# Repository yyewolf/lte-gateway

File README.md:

# lte-gateway

A self-hosted LTE SMS + voice gateway: an ESP32-S3 board with a SIMCom LTE Cat-1 modem
(VoLTE) that joins a Tailscale tailnet over WiFi. It sends and receives SMS and relays
calls as an RTP audio stream. All the heavy logic (Discord bridge, recording, SIP) runs on
a separate machine on the tailnet.

## Layout

| Folder | What |
|---|---|
| `firmware/` | ESP-IDF firmware for the gateway board |
| `hardware/` | KiCad project for the board and its fabrication files ([README](hardware/README.md)) |
| `server/` | Go server: Discord bridge for SMS, calls and call audio ([README](server/README.md)) |
| `case/` | 3D-printable snap-fit enclosure ([README](case/README.md)) |

## Pictures

| Assembly without the lid | Assembly with the lid on |
|---|---|
|  |  |

## Sponsorship

JLCPCB sponsored the PCB fabrication and assembly for this project: I paid much less than the
normal price for the rev 0.6 boards. They have no say in what I write here, and I'm free to
say anything about them, good or bad.

## License

The firmware, server, hardware and case here are BSD 3-Clause, see [LICENSE](LICENSE).

Tailscale compatibility does not come from Tailscale: `firmware/components/microlink` is
vendored from [CamM2325/microlink](https://github.com/CamM2325/microlink) (MIT, upstream
commit 216da33), a reverse-engineered implementation of the Tailscale protocol for embedded
devices, unaffiliated with and not endorsed by Tailscale Inc. The vendored copy carries
local patches (listed in
[firmware/components/VENDORED.txt](firmware/components/VENDORED.txt)), so it is committed
here rather than fetched at build time. `firmware/components/wireguard_lwip` and the x25519
sources keep their own licenses, included next to the code.

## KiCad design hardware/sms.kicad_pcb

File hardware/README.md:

# Hardware

ESP32-S3-WROOM-1 + SIMCom A7670E-LASE gateway board, KiCad 10.

- 4 layers, 99.9 x 99.9 mm, JLC04161H-7628 stackup, ENIG
- Open `sms.kicad_pro`. The JLC symbols, footprints and 3D models are in `lib/`.
- `sms-schematic.pdf` is the schematic exported as a PDF (re-export with `kicad-cli sch export pdf -o sms-schematic.pdf sms.kicad_sch` after edits).
- `schematic-notes.md` has the design notes that used to sit as text on the schematic sheets.
- `fab/rev0.6/` holds the Gerbers, BOM and CPL used for the JLCPCB order.

PCB fabrication and assembly sponsored by JLCPCB.

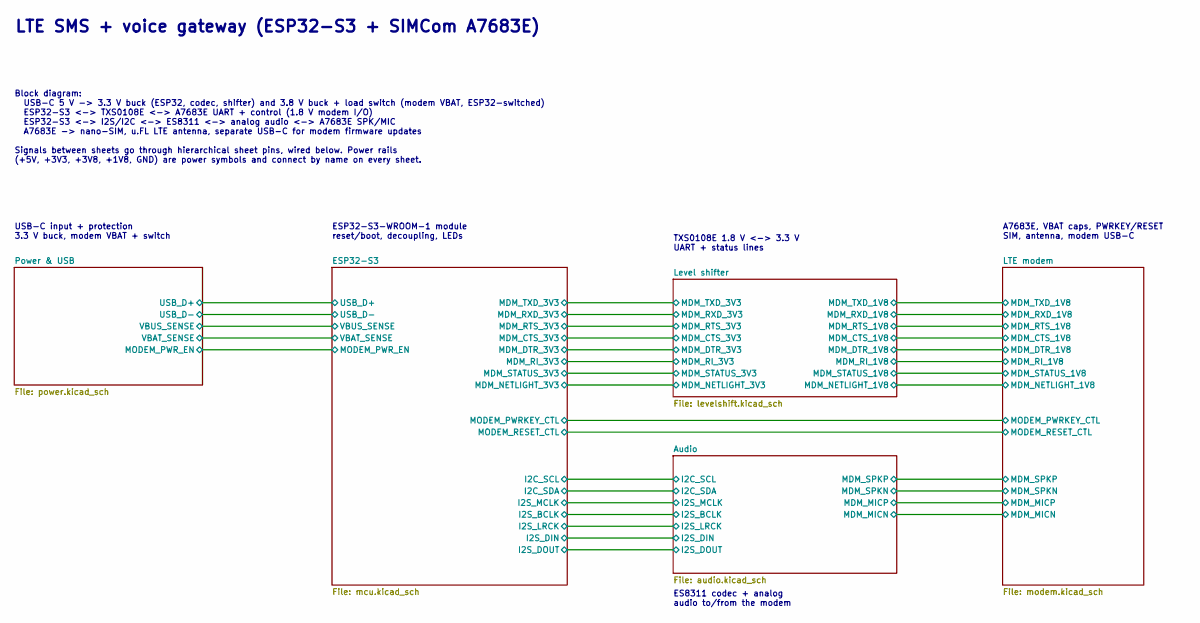
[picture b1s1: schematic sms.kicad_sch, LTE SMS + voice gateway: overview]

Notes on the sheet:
USB-C input + protection 3.3 V buck, modem VBAT + switch
LTE SMS + voice gateway (ESP32-S3 + SIMCom A7683E)
ESP32-S3-WROOM-1 module reset/boot, decoupling, LEDs
A7683E, VBAT caps, PWRKEY/RESET SIM, antenna, modem USB-C
Block diagram: USB-C 5 V -> 3.3 V buck (ESP32, codec, shifter) and 3.8 V buck + load switch (modem VBAT, ESP32-switched) ESP32-S3 <-> TXS0108E <-> A7683E UART + control (1.8 V modem I/O) ESP32-S3 <-> I2S/I2C <-> ES8311 <-> analog audio <-> A7683E SPK/MIC A7683E -> nano-SIM, u.FL LTE antenna, separa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
TXS0108E 1.8 V <-> 3.3 V UART + status lines
ES8311 codec + analog audio to/from the modem

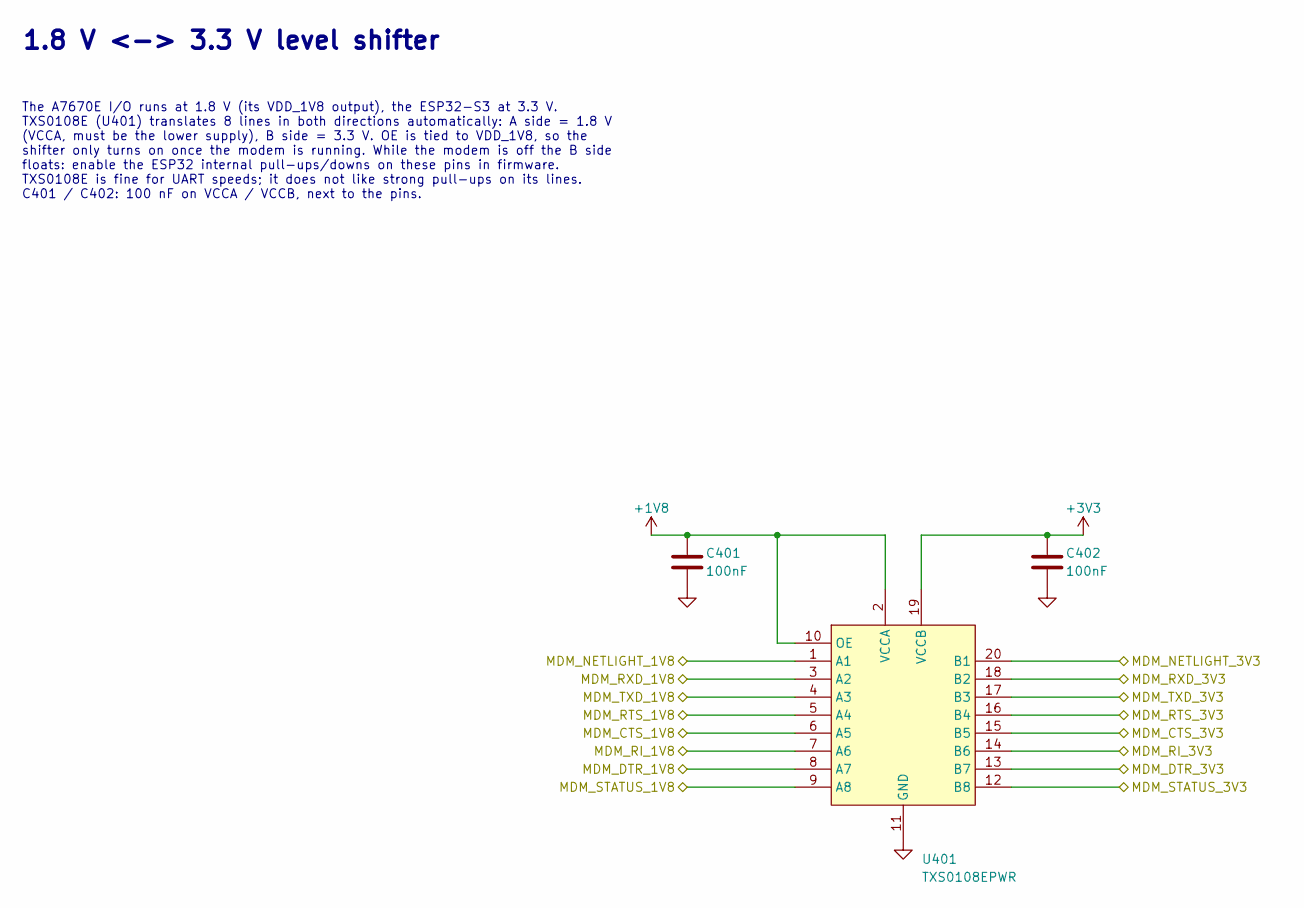
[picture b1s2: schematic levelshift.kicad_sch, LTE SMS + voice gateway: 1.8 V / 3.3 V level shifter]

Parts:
C401, C402: 100nF; C_0402_1005Metric; MPN CL05B104KO5NNNC; LCSC Part C1525
U401: TXS0108EPWR; TSSOP-20_L6.5-W4.4-P0.65-LS6.4-BL; MPN TXS0108EPWR; LCSC Part C17206

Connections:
+1V8: C401.1, U401.2 (VCCA), U401.10 (OE); also elsewhere on the board
+3V3: C402.1, U401.19 (VCCB); also elsewhere on the board
/ESP32-S3/MDM_CTS_3V3: U401.15 (B5); also elsewhere on the board
/ESP32-S3/MDM_DTR_3V3: U401.13 (B7); also elsewhere on the board
/ESP32-S3/MDM_NETLIGHT_3V3: U401.20 (B1); also elsewhere on the board
/ESP32-S3/MDM_RI_3V3: U401.14 (B6); also elsewhere on the board
/ESP32-S3/MDM_RTS_3V3: U401.16 (B4); also elsewhere on the board
/ESP32-S3/MDM_RXD_3V3: U401.18 (B2); also elsewhere on the board
/ESP32-S3/MDM_STATUS_3V3: U401.12 (B8); also elsewhere on the board
/ESP32-S3/MDM_TXD_3V3: U401.17 (B3); also elsewhere on the board
/LTE modem/MDM_CTS_1V8: U401.6 (A5); also elsewhere on the board
/LTE modem/MDM_DTR_1V8: U401.8 (A7); also elsewhere on the board
/LTE modem/MDM_NETLIGHT_1V8: U401.1 (A1); also elsewhere on the board
/LTE modem/MDM_RI_1V8: U401.7 (A6); also elsewhere on the board
/LTE modem/MDM_RTS_1V8: U401.5 (A4); also elsewhere on the board
/LTE modem/MDM_RXD_1V8: U401.3 (A2); also elsewhere on the board
/LTE modem/MDM_STATUS_1V8: U401.9 (A8); also elsewhere on the board
/LTE modem/MDM_TXD_1V8: U401.4 (A3); also elsewhere on the board
GND: C401.2, C402.2, U401.11 (GND); also elsewhere on the board

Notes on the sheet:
The A7670E I/O runs at 1.8 V (its VDD_1V8 output), the ESP32-S3 at 3.3 V. TXS0108E (U401) translates 8 lines in both directions automatically: A side = 1.8 V (VCCA, must be the lower supply), B side = 3.3 V. OE is tied to VDD_1V8, so the shifter only turns on once the modem is running. While the mo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
1.8 V <-> 3.3 V level shifter

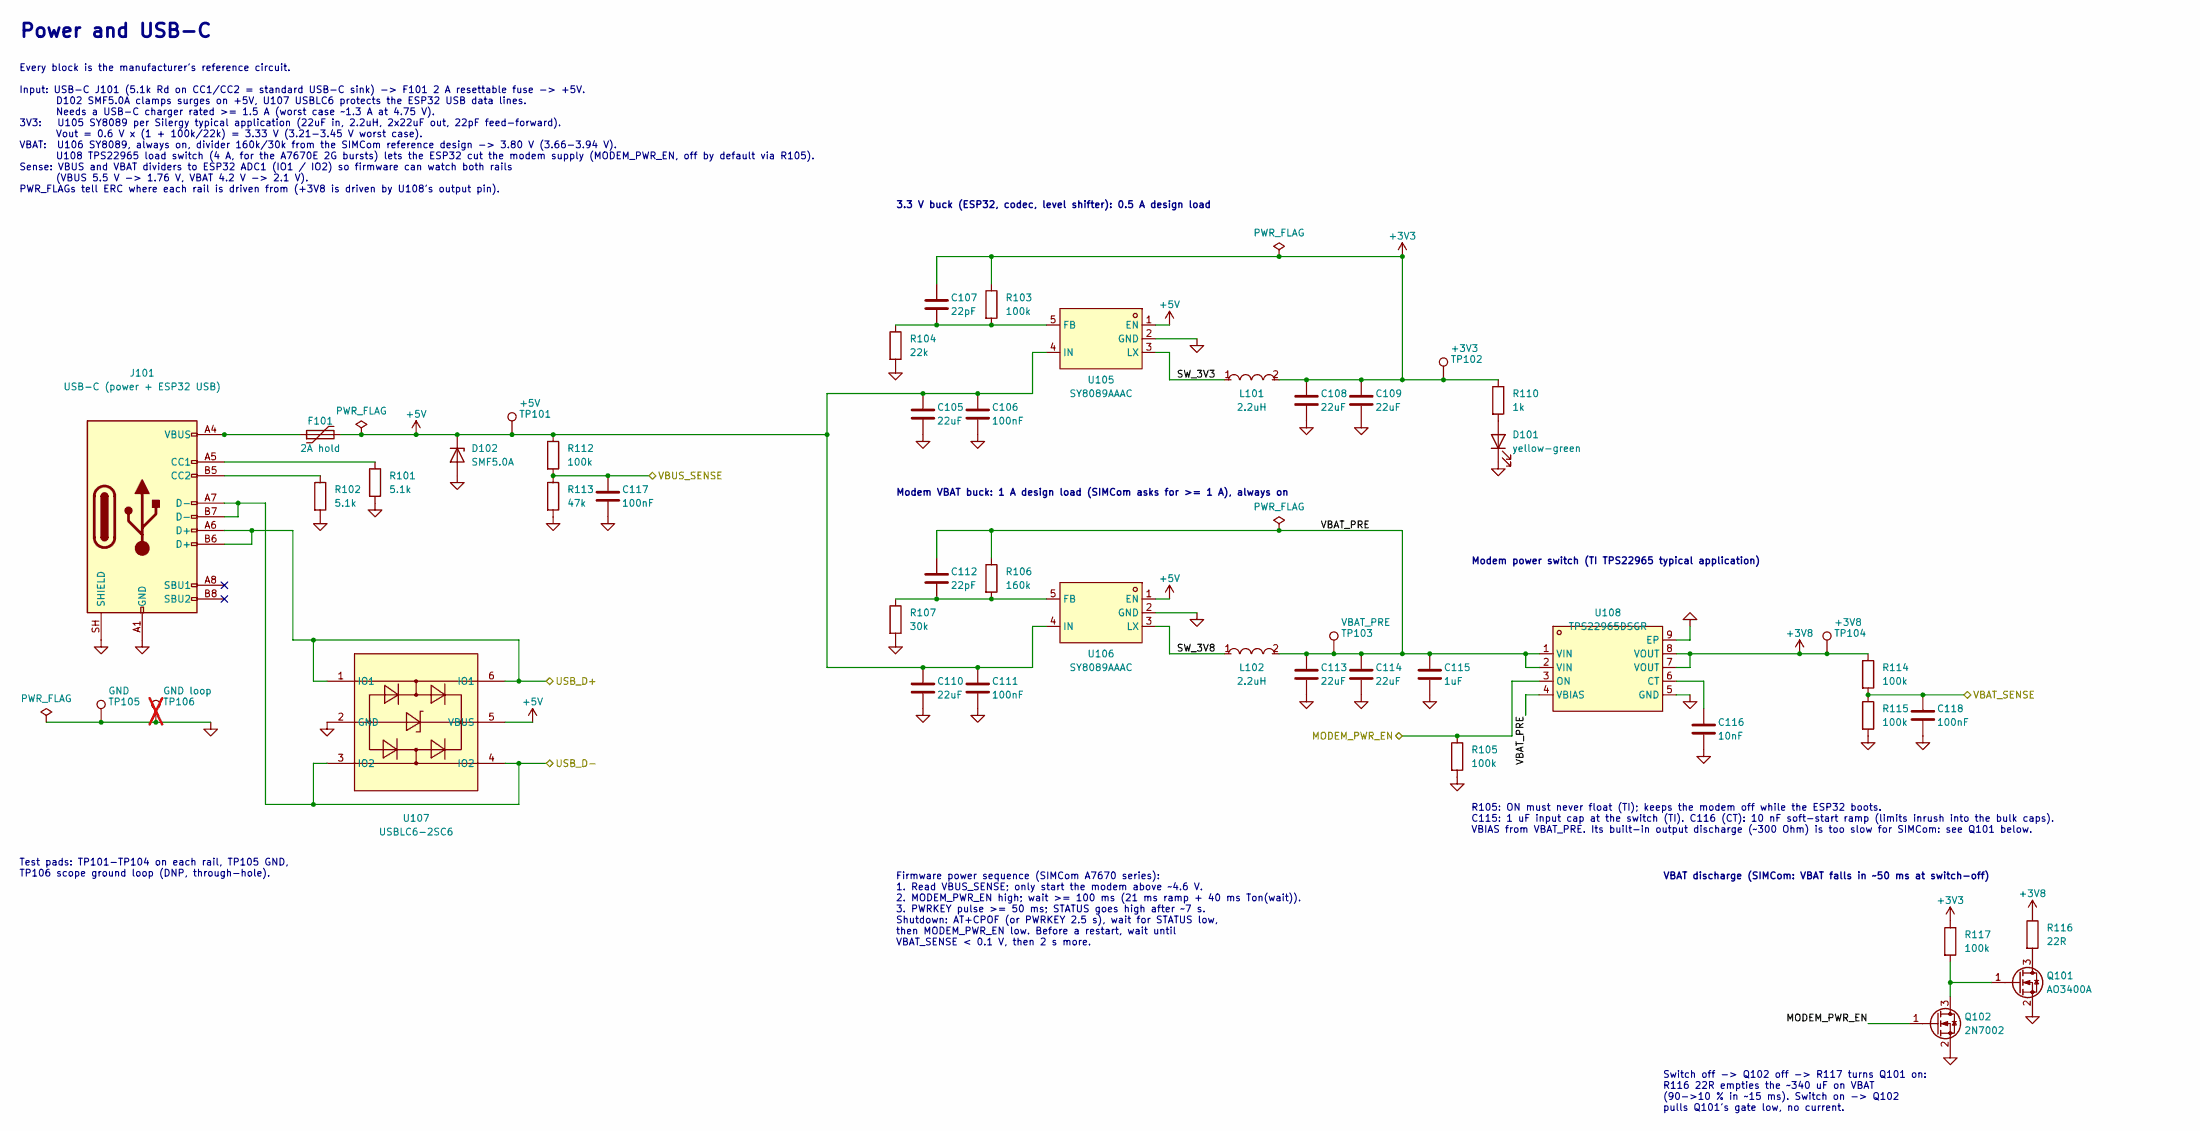
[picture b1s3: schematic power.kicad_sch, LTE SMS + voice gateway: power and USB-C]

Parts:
C105, C108, C109, C110, C113, C114: 22uF; C_0805_2012Metric; MPN CL21A226MAQNNNE; LCSC Part C45783
C106, C111, C117, C118: 100nF; C_0402_1005Metric; MPN CL05B104KO5NNNC; LCSC Part C1525
C107, C112: 22pF; C_0402_1005Metric; MPN 0402CG220J500NT; LCSC Part C1555
C115: 1uF; C_0402_1005Metric; MPN CL05A105KA5NQNC; LCSC Part C52923
C116: 10nF; C_0402_1005Metric; MPN CL05B103KB5NNNC; LCSC Part C15195
D101: yellow-green; LED_0603_1608Metric; MPN KT-0603YG; LCSC Part C2289
D102: SMF5.0A; D_SOD-123F; MPN SMF5.0A; LCSC Part C193402
F101: 2A hold; Fuse_1206_3216Metric; MPN SMD1206P200TF; LCSC Part C20988
J101: USB-C (power + ESP32 USB); USB_C_Receptacle_HRO_TYPE-C-31-M-12; MPN TYPE-C-31-M-12; LCSC Part C165948
L101, L102: 2.2uH; IND-SMD_L4.0-W4.0_FNR40XXS; MPN FNR4030S2R2MT; LCSC Part C167869
Q101: AO3400A; SOT-23-3_L2.9-W1.3-P1.90-LS2.4-BR; MPN AO3400A; LCSC Part C20917
Q102: 2N7002; SOT-23-3_L2.9-W1.3-P1.90-LS2.4-BR; MPN 2N7002; LCSC Part C8545
R101, R102: 5.1k; R_0402_1005Metric; MPN 0402WGF5101TCE; LCSC Part C25905
R103, R105, R112, R114, R115, R117: 100k; R_0402_1005Metric; MPN 0402WGF1003TCE; LCSC Part C25741
R104: 22k; R_0402_1005Metric; MPN 0402WGF2202TCE; LCSC Part C25768
R106: 160k; R_0402_1005Metric; MPN 0402WGF1603TCE; LCSC Part C25757
R107: 30k; R_0402_1005Metric; MPN 0402WGF3002TCE; LCSC Part C25776
R110: 1k; R_0402_1005Metric; MPN 0402WGF1001TCE; LCSC Part C11702
R113: 47k; R_0402_1005Metric; MPN 0402WGF4702TCE; LCSC Part C25792
R116: 22R; R_0805_2012Metric; MPN 0805W8F220JT5E; LCSC Part C17561
TP101: +5V; TestPoint_Pad_D1.5mm; MPN test pad
TP102: +3V3; TestPoint_Pad_D1.5mm; MPN test pad
TP103: VBAT_PRE; TestPoint_Pad_D1.5mm; MPN test pad
TP104: +3V8; TestPoint_Pad_D1.5mm; MPN test pad
TP105: GND; TestPoint_Pad_D1.5mm; MPN test pad
TP106: GND loop; TestPoint_Keystone_5000-5004_Miniature; MPN Keystone 5001; not fitted
U105, U106: SY8089AAAC; SOT-23-5_L3.0-W1.7-P0.95-LS2.8-BR; MPN SY8089AAAC; LCSC Part C78988
U107: USBLC6-2SC6; SOT-23-6_L2.9-W1.6-P0.95-LS2.8-BL; MPN USBLC6-2SC6; LCSC Part C7519
U108: TPS22965DSGR; UDFN-8_L2.0-W2.0-P0.50-TL-EP; MPN TPS22965DSGR; LCSC Part C122837

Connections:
+3V3: C107.1, C108.1, C109.1, L101.2, R103.1, R110.1, R117.1, TP102.1; also elsewhere on the board
+3V8: R114.1, R116.1, TP104.1, U108.7 (VOUT), U108.8 (VOUT); also elsewhere on the board
+5V: C105.1, C106.1, C110.1, C111.1, D102.1 (K), F101.2, R112.1, TP101.1, U105.1 (EN), U105.4 (IN), U106.1 (EN), U106.4 (IN), U107.5 (VBUS)
/ESP32-S3/USB_D+: J101.A6 (D+), J101.B6 (D+), U107.1 (IO1), U107.6 (IO1); also elsewhere on the board
/ESP32-S3/USB_D-: J101.A7 (D-), J101.B7 (D-), U107.3 (IO2), U107.4 (IO2); also elsewhere on the board
/ESP32-S3/VBAT_SENSE: C118.1, R114.2, R115.1; also elsewhere on the board
/ESP32-S3/VBUS_SENSE: C117.1, R112.2, R113.1; also elsewhere on the board
/Power & USB/MODEM_PWR_EN: Q102.1 (G), R105.1, U108.3 (ON); also elsewhere on the board
/Power & USB/SW_3V3: L101.1, U105.3 (LX)
/Power & USB/SW_3V8: L102.1, U106.3 (LX)
/Power & USB/VBAT_PRE: C112.1, C113.1, C114.1, C115.1, L102.2, R106.1, TP103.1, U108.1 (VIN), U108.2 (VIN), U108.4 (VBIAS)
GND: C105.2, C106.2, C108.2, C109.2, C110.2, C111.2, C113.2, C114.2, C115.2, C116.2, C117.2, C118.2, D101.1 (K), D102.2 (A), J101.A1 (GND), J101.A12 (GND), J101.B1 (GND), J101.B12 (GND), J101.SH (SHIELD), Q101.2 (S), Q102.2 (S), R101.2, R102.2, R104.2, R105.2, R107.2, R113.2, R115.2, TP105.1, TP106.1, U105.2 (GND), U106.2 (GND), U107.2 (GND), U108.5 (GND), U108.9 (EP); also elsewhere on the board
unnamed: D101.2 (A), R110.2
unnamed: F101.1, J101.A4 (VBUS), J101.A9 (VBUS), J101.B4 (VBUS), J101.B9 (VBUS)
unnamed: J101.A5 (CC1), R101.1
unnamed: J101.B5 (CC2), R102.1
unnamed: Q101.3 (D), R116.2
unnamed: Q101.1 (G), Q102.3 (D), R117.2
unnamed: C107.2, R103.2, R104.1, U105.5 (FB)
unnamed: C112.2, R106.2, R107.1, U106.5 (FB)
unnamed: C116.1, U108.6 (CT)

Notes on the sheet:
Power and USB-C
Every block is the manufacturer's reference circuit. Input: USB-C J101 (5.1k Rd on CC1/CC2 = standard USB-C sink) -> F101 2 A resettable fuse -> +5V. D102 SMF5.0A clamps surges on +5V, U107 USBLC6 protects the ESP32 USB data lines. Needs a USB-C charger rated >= 1.5 A (worst case ~1.3 A at 4.75 V).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
3.3 V buck (ESP32, codec, level shifter): 0.5 A design load
Modem VBAT buck: 1 A design load (SIMCom asks for >= 1 A), always on
Modem power switch (TI TPS22965 typical application)
R105: ON must never float (TI); keeps the modem off while the ESP32 boots. C115: 1 uF input cap at the switch (TI). C116 (CT): 10 nF soft-start ramp (limits inrush into the bulk caps). VBIAS from VBAT_PRE. Its built-in output discharge (~300 Ohm) is too slow for SIMCom: see Q101 below.
VBAT discharge (SIMCom: VBAT falls in ~50 ms at switch-off)
Switch off -> Q102 off -> R117 turns Q101 on: R116 22R empties the ~340 uF on VBAT (90->10 % in ~15 ms). Switch on -> Q102 pulls Q101's gate low, no current.
Firmware power sequence (SIMCom A7670 series): 1. Read VBUS_SENSE; only start the modem above ~4.6 V. 2. MODEM_PWR_EN high; wait >= 100 ms (21 ms ramp + 40 ms Ton(wait)). 3. PWRKEY pulse >= 50 ms; STATUS goes high after ~7 s. Shutdown: AT+CPOF (or PWRKEY 2.5 s), wait for STATUS low, then MODEM_PWR_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
Test pads: TP101-TP104 on each rail, TP105 GND, TP106 scope ground loop (DNP, through-hole).

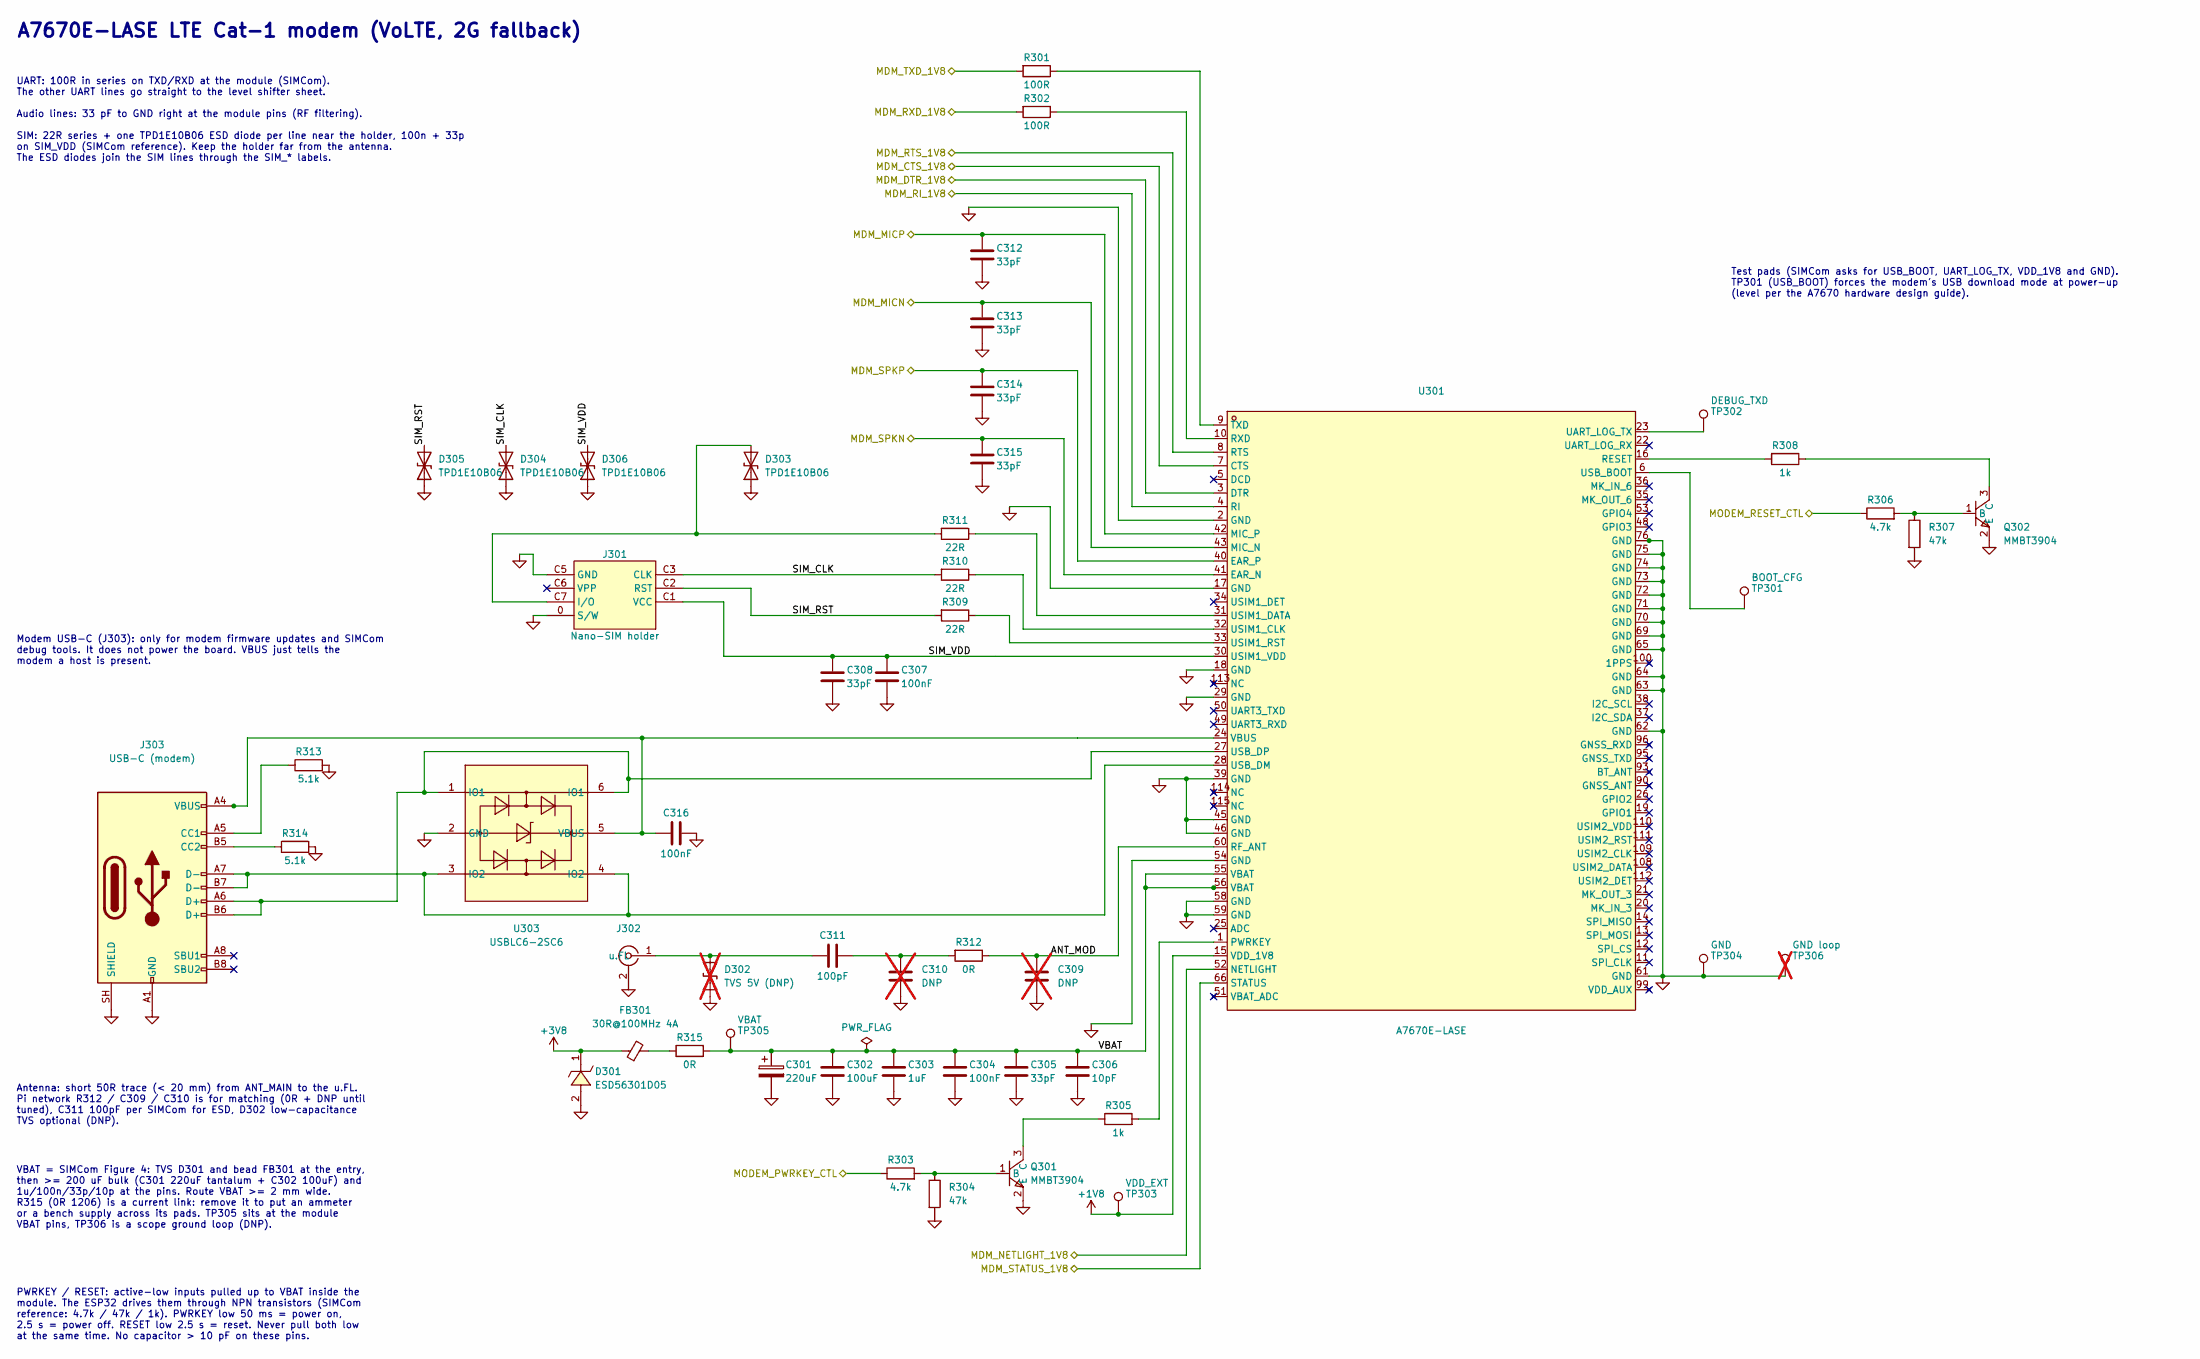
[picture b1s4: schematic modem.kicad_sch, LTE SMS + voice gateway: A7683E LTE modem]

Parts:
C301: 220uF; CP_EIA-7343-31_Kemet-D; MPN TAJD227K010RNJ (220uF 10V tantalum, 500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; LCSC Part C8024
C302: 100uF; C_1206_3216Metric; MPN CL31A107MQHNNNE; LCSC Part C15008
C303: 1uF; C_0402_1005Metric; MPN CL05A105KA5NQNC; LCSC Part C52923
C304, C307, C316: 100nF; C_0402_1005Metric; MPN CL05B104KO5NNNC; LCSC Part C1525
C305, C308, C312, C313, C314, C315: 33pF; C_0402_1005Metric; MPN 0402CG330J500NT; LCSC Part C1562
C306: 10pF; C_0402_1005Metric; MPN CL05C100JB5NNNC; LCSC Part C32949
C309, C310: DNP; C_0402_1005Metric; MPN matching, value from antenna tuning; not fitted
C311: 100pF; C_0402_1005Metric; MPN 0402CG101J500NT; LCSC Part C1546
D301: ESD56301D05; DFN1610-2L_L1.6-W1.0-P1.10-RD; MPN ESD56301D05-2/TR; LCSC Part C2939837
D302: TVS 5V (DNP); D_SOD-323; MPN choose at review; not fitted
D303, D304, D305, D306: TPD1E10B06; X1SON-2_L1.0-W0.6-P0.65-BI-1; MPN TPD1E10B06DPYR; LCSC Part C48260
FB301: 30R@100MHz 4A; L_0805_2012Metric; MPN BLM21PG300SN1D; LCSC Part C16903
J301: Nano-SIM holder; SIM-SMD_C77877; MPN NANO SIM 6PIN; LCSC Part C2963104
J302: u.FL; U.FL_Hirose_U.FL-R-SMT-1_Vertical; MPN U.FL-R-SMT-1(80); LCSC Part C88374
J303: USB-C (modem); USB_C_Receptacle_HRO_TYPE-C-31-M-12; MPN TYPE-C-31-M-12; LCSC Part C165948
Q301, Q302: MMBT3904; SOT-23-3_L2.9-W1.3-P1.90-LS2.4-BR; MPN MMBT3904; LCSC Part C20526
R301, R302: 100R; R_0402_1005Metric; MPN 0402WGF1000TCE; LCSC Part C25076
R303, R306: 4.7k; R_0402_1005Metric; MPN 0402WGF4701TCE; LCSC Part C25900
R304, R307: 47k; R_0402_1005Metric; MPN 0402WGF4702TCE; LCSC Part C25792
R305, R308: 1k; R_0402_1005Metric; MPN 0402WGF1001TCE; LCSC Part C11702
R309, R310, R311: 22R; R_0402_1005Metric; MPN 0402WGF220JTCE; LCSC Part C25092
R312: 0R; R_0402_1005Metric; MPN 0402WGF0000TCE; LCSC Part C17168
R313, R314: 5.1k; R_0402_1005Metric; MPN 0402WGF5101TCE; LCSC Part C25905
R315: 0R; R_1206_3216Metric; MPN 1206W4F0000T5E; LCSC Part C17888
TP301: BOOT_CFG; TestPoint_Pad_D1.5mm; MPN test pad
TP302: DEBUG_TXD; TestPoint_Pad_D1.5mm; MPN test pad
TP303: VDD_EXT; TestPoint_Pad_D1.5mm; MPN test pad
TP304: GND; TestPoint_Pad_D1.5mm; MPN test pad
TP305: VBAT; TestPoint_Pad_D1.5mm
TP306: GND loop; TestPoint_Keystone_5000-5004_Miniature; MPN Keystone 5001; not fitted
U301: A7670E-LASE; LGA-124_L24.0-W24.0-P1.0-A7670C-LASS; MPN A7670E-LASE; LCSC Part C5362211
U303: USBLC6-2SC6; SOT-23-6_L2.9-W1.6-P0.95-LS2.8-BL; MPN USBLC6-2SC6; LCSC Part C7519

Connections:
+1V8: TP303.1, U301.15 (VDD_1V8); also elsewhere on the board
+3V8: D301.1 (K), FB301.1; also elsewhere on the board
/Audio/MDM_MICN: C313.1, U301.43 (MIC_N); also elsewhere on the board
/Audio/MDM_MICP: C312.1, U301.42 (MIC_P); also elsewhere on the board
/Audio/MDM_SPKN: C315.1, U301.41 (EAR_N); also elsewhere on the board
/Audio/MDM_SPKP: C314.1, U301.40 (EAR_P); also elsewhere on the board
/ESP32-S3/MODEM_PWRKEY_CTL: R303.1; also elsewhere on the board
/ESP32-S3/MODEM_RESET_CTL: R306.1; also elsewhere on the board
/LTE modem/ANT_MOD: C309.1, R312.1, U301.60 (RF_ANT)
/LTE modem/MDM_CTS_1V8: U301.7 (CTS); also elsewhere on the board
/LTE modem/MDM_DTR_1V8: U301.3 (DTR); also elsewhere on the board
/LTE modem/MDM_NETLIGHT_1V8: U301.52 (NETLIGHT); also elsewhere on the board
/LTE modem/MDM_RI_1V8: U301.4 (RI); also elsewhere on the board
/LTE modem/MDM_RTS_1V8: U301.8 (RTS); also elsewhere on the board
/LTE modem/MDM_RXD_1V8: R302.2; also elsewhere on the board
/LTE modem/MDM_STATUS_1V8: U301.66 (STATUS); also elsewhere on the board
/LTE modem/MDM_TXD_1V8: R301.2; also elsewhere on the board
/LTE modem/SIM_CLK: D304.2 (A2), J301.C3 (CLK), R310.2
/LTE modem/SIM_RST: D305.2 (A2), J301.C2 (RST), R309.2
/LTE modem/SIM_VDD: C307.1, C308.1, D306.2 (A2), J301.C1 (VCC), U301.30 (USIM1_VDD)
/LTE modem/VBAT: C301.1, C302.1, C303.1, C304.1, C305.1, C306.1, R315.2, TP305.1, U301.55 (VBAT), U301.56 (VBAT), U301.57 (VBAT)
GND: C301.2, C302.2, C303.2, C304.2, C305.2, C306.2, C307.2, C308.2, C309.2, C310.2, C312.2, C313.2, C314.2, C315.2, C316.2, D301.2 (A), D302.1 (A1), D303.1 (A1), D304.1 (A1), D305.1 (A1), D306.1 (A1), J301.0 (S/W), J301.C5 (GND), J302.2 (Ext), J303.A1 (GND), J303.A12 (GND), J303.B1 (GND), J303.B12 (GND), J303.SH (SHIELD), Q301.2 (E), Q302.2 (E), R304.2, R307.2, R313.2, R314.2, TP304.1, TP306.1, U301.2 (GND), U301.17 (GND), U301.18 (GND), U301.29 (GND), U301.39 (GND), U301.45 (GND), U301.46 (GND), U301.54 (GND), U301.58 (GND), U301.59 (GND), U301.61 (GND), U301.62 (GND), U301.63 (GND), U301.64 (GND), U301.65 (GND), U301.69 (GND), U301.70 (GND), U301.71 (GND), U301.72 (GND), U301.73 (GND), U301.74 (GND), U301.75 (GND), U301.76 (GND), U301.77 (GND), U301.78 (GND), U301.79 (GND), U301.80 (GND), U301.81 (GND), U301.82 (GND), U301.83 (GND), U301.84 (GND), U301.85 (GND), U301.86 (GND), U301.87 (GND), U301.88 (GND), U301.89 (GND), U301.91 (GND), U301.92 (GND), U301.94 (GND), U303.2 (GND); also elsewhere on the board
unnamed: C310.1, C311.1, R312.2
unnamed: C311.2, D302.2 (A2), J302.1 (In)
unnamed: D303.2 (A2), J301.C7 (I/O), R311.2
unnamed: FB301.2, R315.1
unnamed: J303.A5 (CC1), R313.1
unnamed: J303.B5 (CC2), R314.1
unnamed: Q301.1 (B), R303.2, R304.1
unnamed: Q301.3 (C), R305.1
unnamed: Q302.1 (B), R306.2, R307.1
unnamed: Q302.3 (C), R308.1
unnamed: R305.2, U301.1 (PWRKEY)
unnamed: R308.2, U301.16 (RESET)
unnamed: R302.1, U301.10 (RXD)
unnamed: R301.1, U301.9 (TXD)
unnamed: TP302.1, U301.23 (UART_LOG_TX)
unnamed: TP301.1, U301.6 (USB_BOOT)
unnamed: J303.A7 (D-), J303.B7 (D-), U301.28 (USB_DM), U303.3 (IO2), U303.4 (IO2)
unnamed: J303.A6 (D+), J303.B6 (D+), U301.27 (USB_DP), U303.1 (IO1), U303.6 (IO1)
unnamed: R310.1, U301.32 (USIM1_CLK)
unnamed: R311.1, U301.31 (USIM1_DATA)
unnamed: R309.1, U301.33 (USIM1_RST)
unnamed: C316.1, J303.A4 (VBUS), J303.A9 (VBUS), J303.B4 (VBUS), J303.B9 (VBUS), U301.24 (VBUS), U303.5 (VBUS)

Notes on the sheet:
A7670E-LASE LTE Cat-1 modem (VoLTE, 2G fallback)
UART: 100R in series on TXD/RXD at the module (SIMCom). The other UART lines go straight to the level shifter sheet. Audio lines: 33 pF to GND right at the module pins (RF filtering). SIM: 22R series + one TPD1E10B06 ESD diode per line near the holder, 100n + 33p on SIM_VDD (SIMCom reference). Keep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
Modem USB-C (J303): only for modem firmware updates and SIMCom debug tools. It does not power the board. VBUS just tells the modem a host is present.
Antenna: short 50R trace (< 20 mm) from ANT_MAIN to the u.FL. Pi network R312 / C309 / C310 is for matching (0R + DNP until tuned), C311 100pF per SIMCom for ESD, D302 low-capacitance TVS optional (DNP).
VBAT = SIMCom Figure 4: TVS D301 and bead FB301 at the entry, then >= 200 uF bulk (C301 220uF tantalum + C302 100uF) and 1u/100n/33p/10p at the pins. Route VBAT >= 2 mm wide. R315 (0R 1206) is a current link: remove it to put an ammeter or a bench supply across its pads. TP305 sits at the module VB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
PWRKEY / RESET: active-low inputs pulled up to VBAT inside the module. The ESP32 drives them through NPN transistors (SIMCom reference: 4.7k / 47k / 1k). PWRKEY low 50 ms = power on, 2.5 s = power off. RESET low 2.5 s = reset. Never pull both low at the same time. No capacitor > 10 pF on these pins.
Test pads (SIMCom asks for USB_BOOT, UART_LOG_TX, VDD_1V8 and GND). TP301 (USB_BOOT) forces the modem's USB download mode at power-up (level per the A7670 hardware design guide).

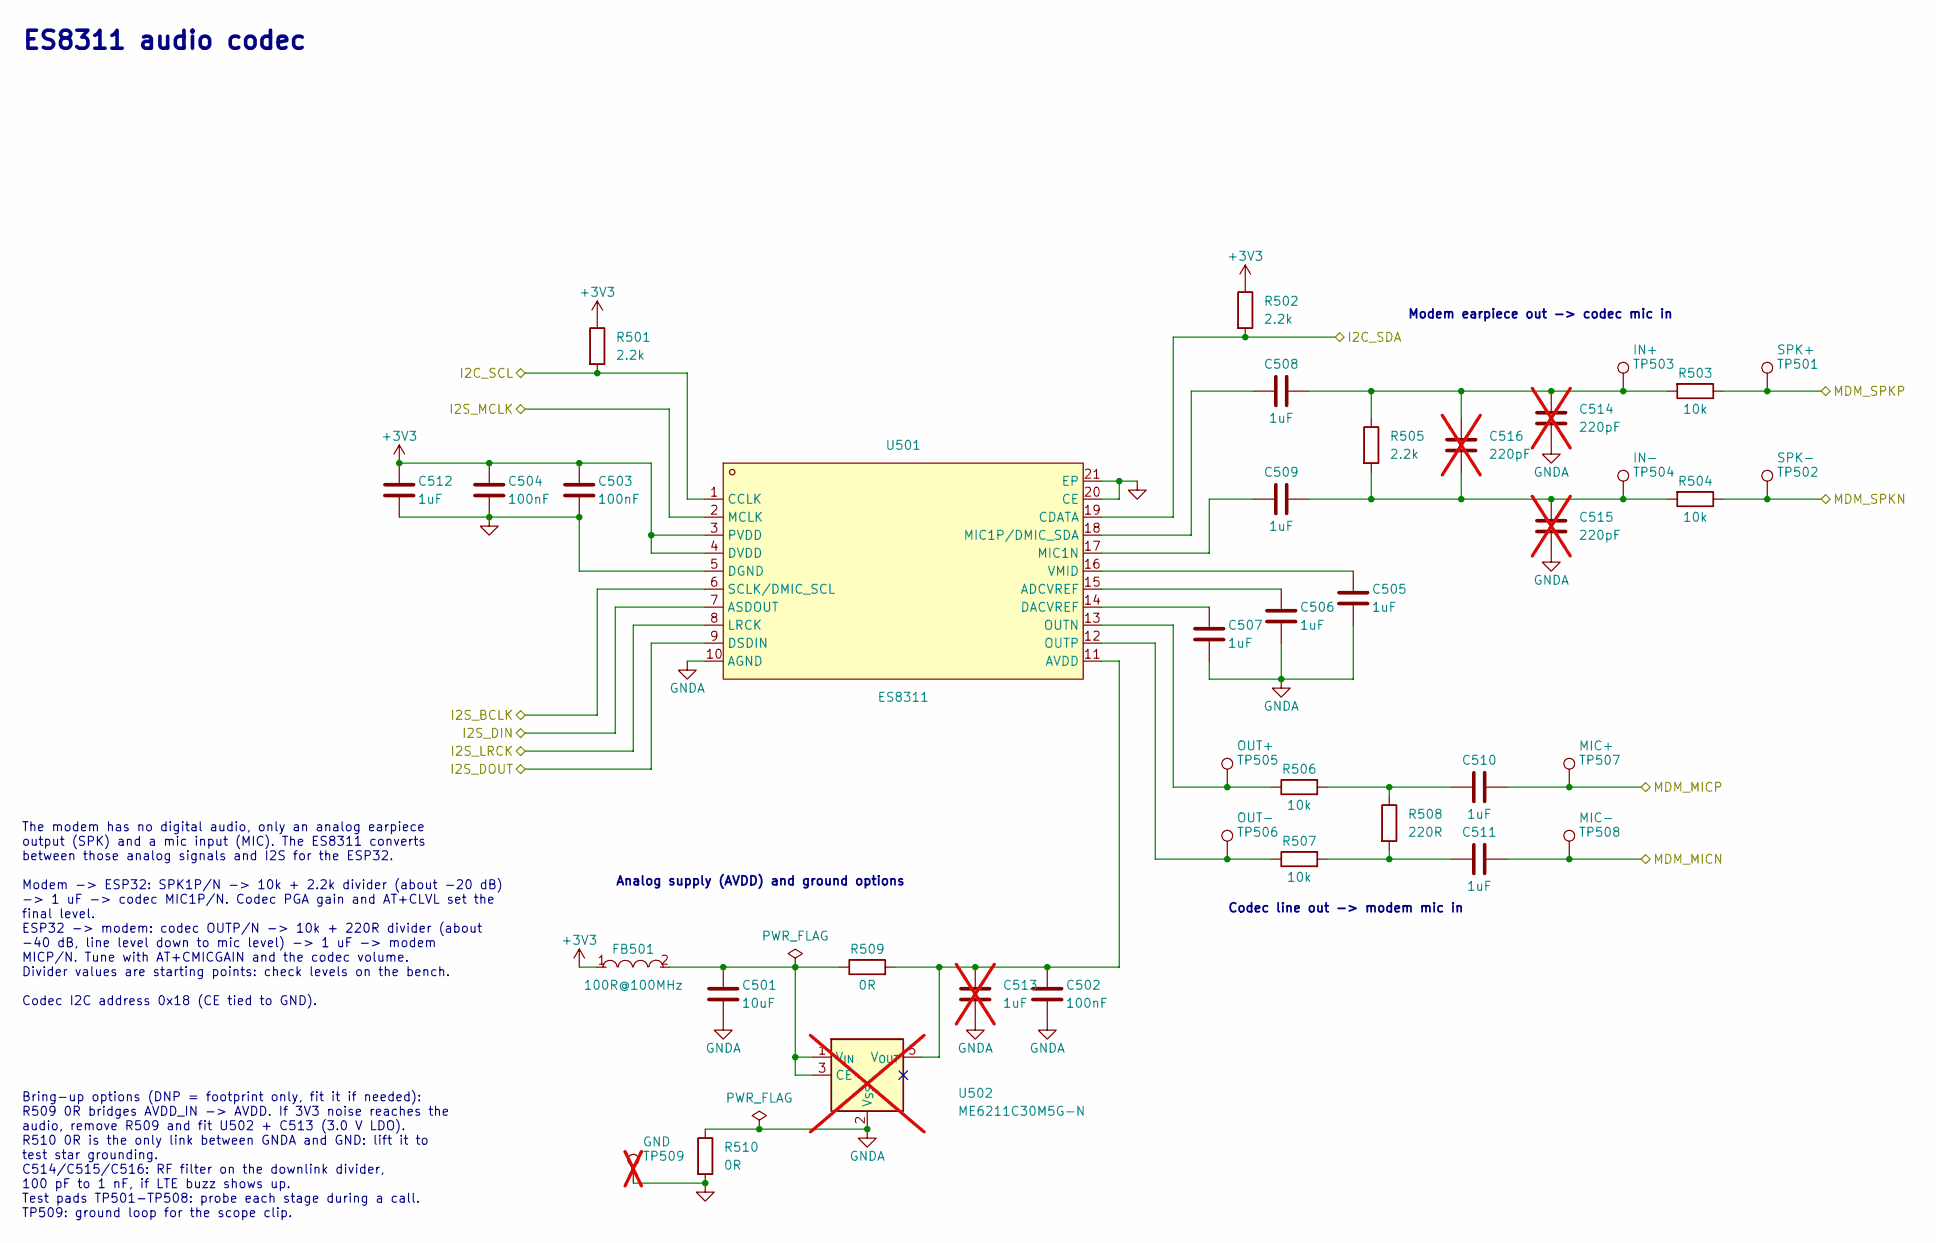
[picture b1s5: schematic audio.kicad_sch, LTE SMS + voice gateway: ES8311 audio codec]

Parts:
C501: 10uF; C_0603_1608Metric; MPN CL10A106KP8NNNC; LCSC Part C19702
C502, C503, C504: 100nF; C_0402_1005Metric; MPN CL05B104KO5NNNC; LCSC Part C1525
C505, C506, C507, C508, C509, C510, C511, C512: 1uF; C_0402_1005Metric; MPN CL05A105KA5NQNC; LCSC Part C52923
C513: 1uF; C_0402_1005Metric; MPN CL05A105KA5NQNC; LCSC Part C52923; not fitted
C514, C515, C516: 220pF; C_0402_1005Metric; MPN C0G 50V, 100pF..1nF; not fitted
FB501: 100R@100MHz; L0805; MPN GZ2012D101TF; LCSC Part C1015
R501, R502, R505: 2.2k; R_0402_1005Metric; MPN 0402WGF2201TCE; LCSC Part C25879
R503, R504, R506, R507: 10k; R_0402_1005Metric; MPN 0402WGF1002TCE; LCSC Part C25744
R508: 220R; R_0402_1005Metric; MPN 0402WGF2200TCE; LCSC Part C25091
R509: 0R; R_0402_1005Metric; MPN 0402WGF0000TCE; LCSC Part C17168
R510: 0R; R_0603_1608Metric; MPN 0603WAF0000T5E; LCSC Part C21189
TP501: SPK+; TestPoint_Pad_D1.0mm
TP502: SPK-; TestPoint_Pad_D1.0mm
TP503: IN+; TestPoint_Pad_D1.0mm
TP504: IN-; TestPoint_Pad_D1.0mm
TP505: OUT+; TestPoint_Pad_D1.0mm
TP506: OUT-; TestPoint_Pad_D1.0mm
TP507: MIC+; TestPoint_Pad_D1.0mm
TP508: MIC-; TestPoint_Pad_D1.0mm
TP509: GND; TestPoint_Keystone_5000-5004_Miniature; MPN Keystone 5001; not fitted
U501: ES8311; WQFN-20_L3.0-W3.0-P0.40-BL-EP1.7; MPN ES8311; LCSC Part C962342
U502: ME6211C30M5G-N; SOT-23-5; MPN ME6211C30M5G-N; LCSC Part C403651; not fitted

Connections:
+3V3: C503.1, C504.1, C512.1, FB501.1, R501.1, R502.1, U501.3 (PVDD), U501.4 (DVDD); also elsewhere on the board
/Audio/I2C_SCL: R501.2, U501.1 (CCLK); also elsewhere on the board
/Audio/I2C_SDA: R502.2, U501.19 (CDATA); also elsewhere on the board
/Audio/I2S_BCLK: U501.6 (SCLK/DMIC_SCL); also elsewhere on the board
/Audio/I2S_DIN: U501.7 (ASDOUT); also elsewhere on the board
/Audio/I2S_DOUT: U501.9 (DSDIN); also elsewhere on the board
/Audio/I2S_LRCK: U501.8 (LRCK); also elsewhere on the board
/Audio/I2S_MCLK: U501.2 (MCLK); also elsewhere on the board
/Audio/MDM_MICN: C511.2, TP508.1; also elsewhere on the board
/Audio/MDM_MICP: C510.2, TP507.1; also elsewhere on the board
/Audio/MDM_SPKN: R504.1, TP502.1; also elsewhere on the board
/Audio/MDM_SPKP: R503.1, TP501.1; also elsewhere on the board
GND: C503.2, C504.2, C512.2, R510.2, TP509.1, U501.5 (DGND), U501.20 (CE), U501.21 (EP); also elsewhere on the board
GNDA: C501.2, C502.2, C505.2, C506.2, C507.2, C513.2, C514.2, C515.2, R510.1, U501.10 (AGND), U502.2 (V_{SS})
unnamed: C508.1, C514.1, C516.1, R503.2, R505.1, TP503.1
unnamed: C509.1, C515.1, C516.2, R504.2, R505.2, TP504.1
unnamed: C510.1, R506.2, R508.1
unnamed: C511.1, R507.2, R508.2
unnamed: C506.1, U501.15 (ADCVREF)
unnamed: C502.1, C513.1, R509.2, U501.11 (AVDD), U502.5 (V_{OUT})
unnamed: C507.1, U501.14 (DACVREF)
unnamed: C509.2, U501.17 (MIC1N)
unnamed: C508.2, U501.18 (MIC1P/DMIC_SDA)
unnamed: R506.1, TP505.1, U501.13 (OUTN)
unnamed: R507.1, TP506.1, U501.12 (OUTP)
unnamed: C505.1, U501.16 (VMID)
unnamed: C501.1, FB501.2, R509.1, U502.1 (V_{IN}), U502.3 (CE)

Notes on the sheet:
Bring-up options (DNP = footprint only, fit it if needed): R509 0R bridges AVDD_IN -> AVDD. If 3V3 noise reaches the audio, remove R509 and fit U502 + C513 (3.0 V LDO). R510 0R is the only link between GNDA and GND: lift it to test star grounding. C514/C515/C516: RF filter on the downlink divider, 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
ES8311 audio codec
Modem earpiece out -> codec mic in
Codec line out -> modem mic in
The modem has no digital audio, only an analog earpiece output (SPK) and a mic input (MIC). The ES8311 converts between those analog signals and I2S for the ESP32. Modem -> ESP32: SPK1P/N -> 10k + 2.2k divider (about -20 dB) -> 1 uF -> codec MIC1P/N. Codec PGA gain and AT+CLVL set the final level. 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
Analog supply (AVDD) and ground options
